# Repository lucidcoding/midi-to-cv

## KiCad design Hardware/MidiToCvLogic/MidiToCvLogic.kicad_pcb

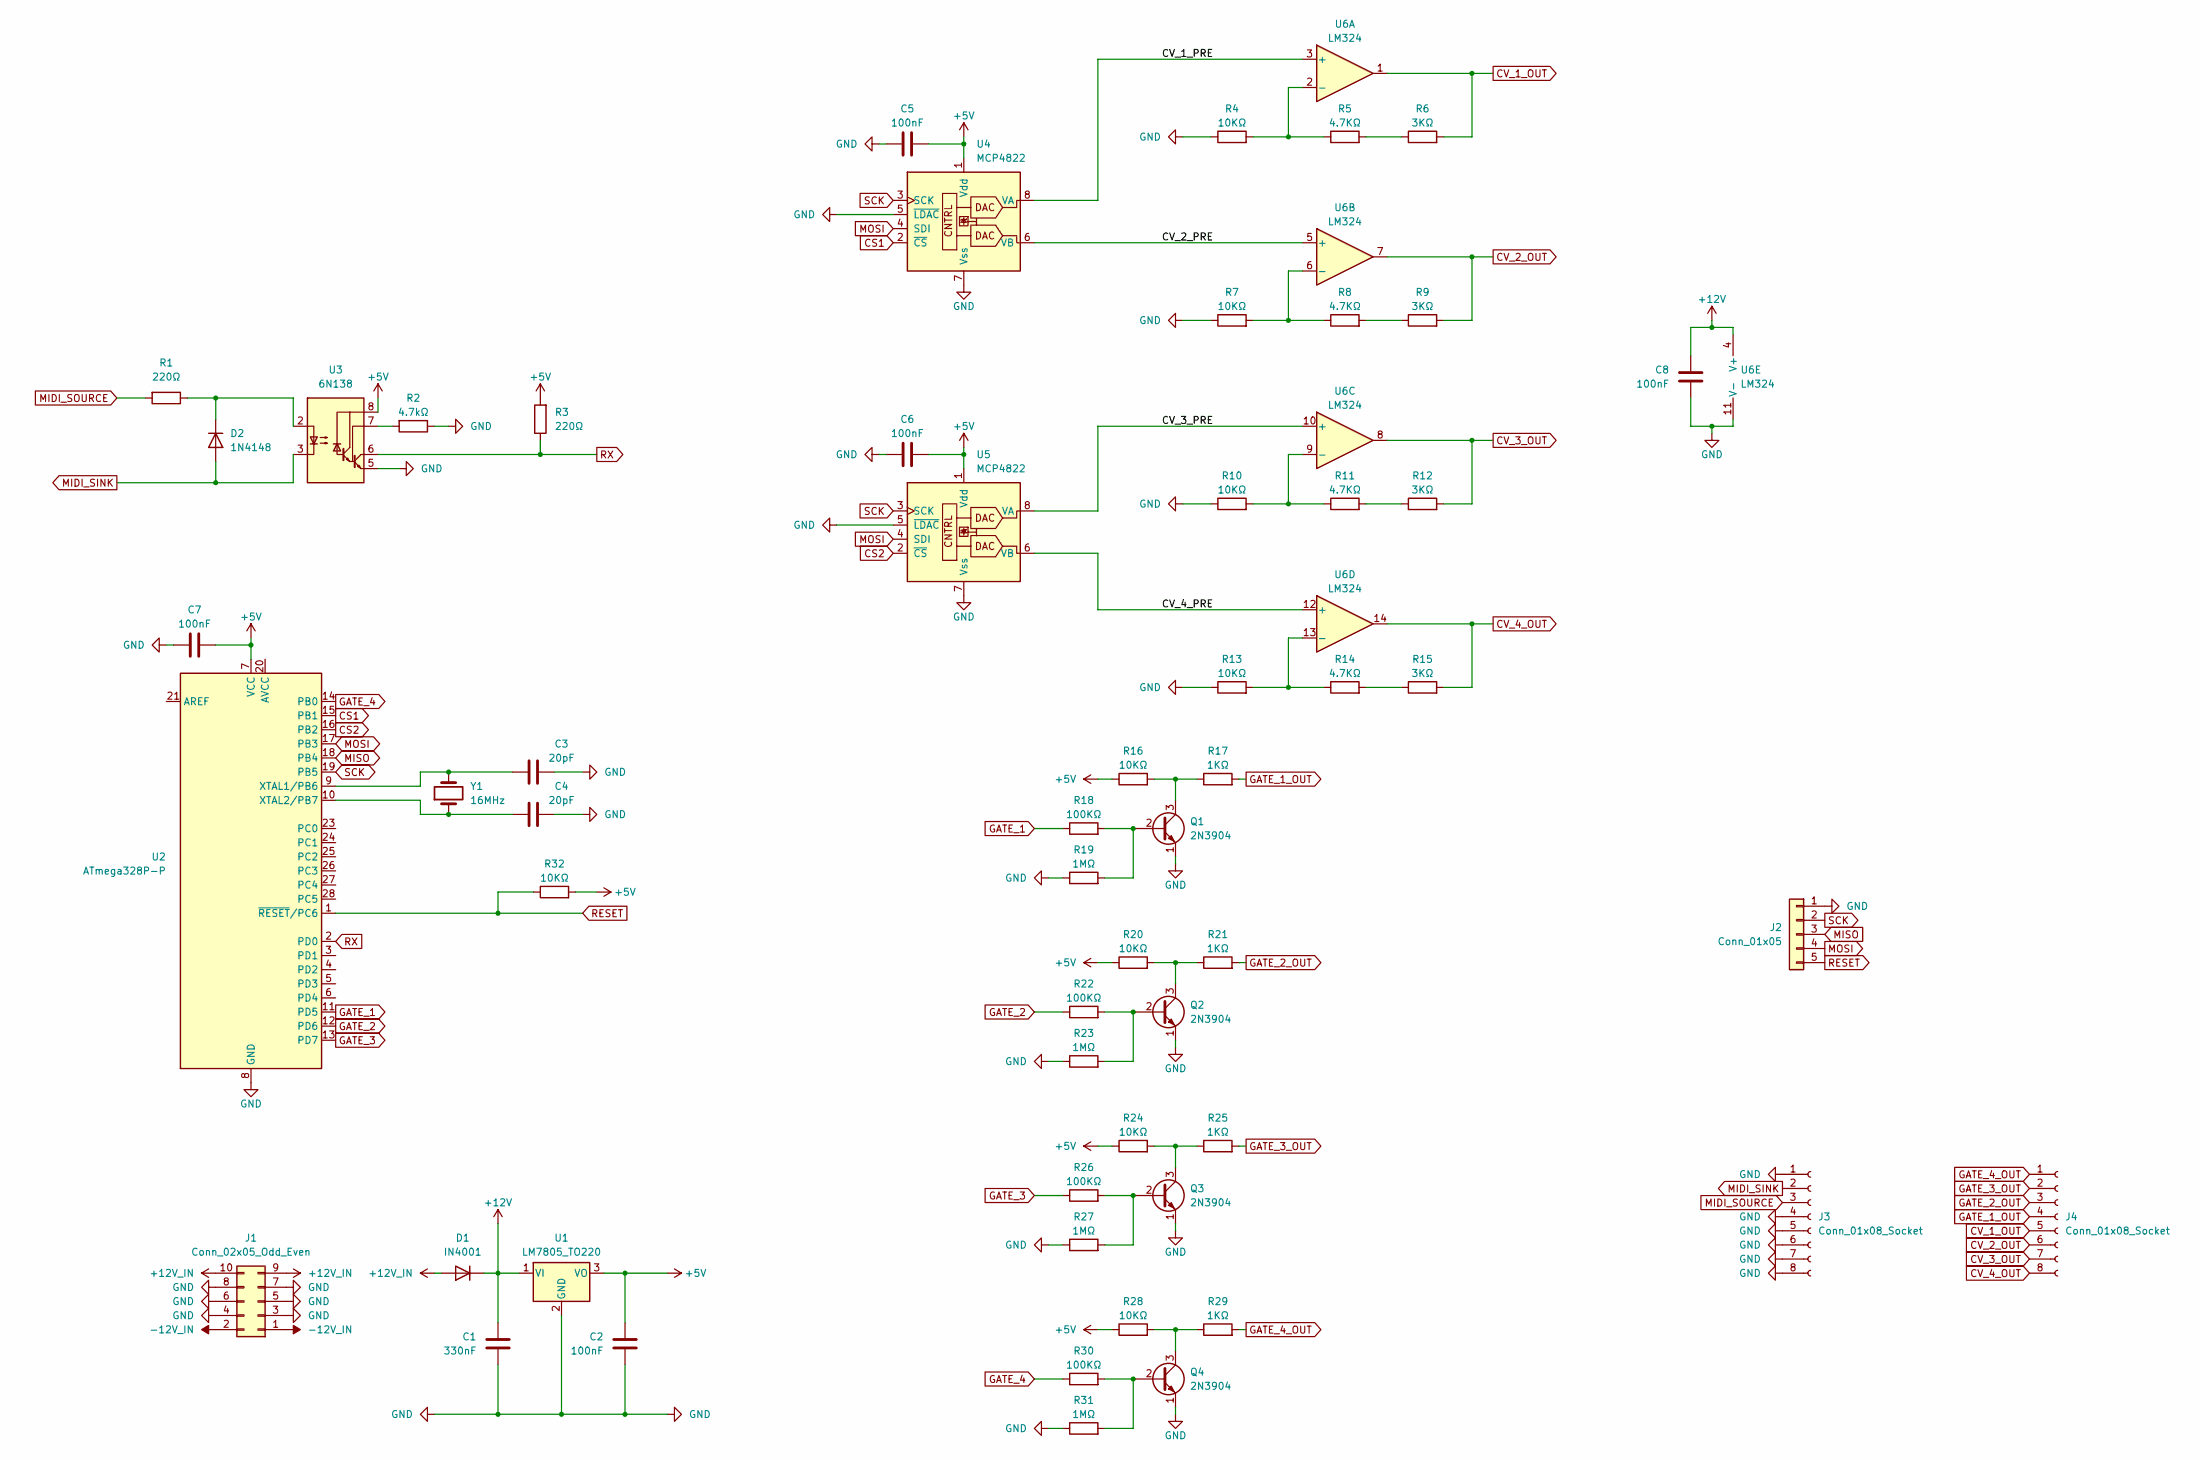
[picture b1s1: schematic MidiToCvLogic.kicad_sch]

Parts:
C1: 330nF; C_Disc_D5.0mm_W2.5mm_P5.00mm
C2, C8: 100nF; C_Disc_D5.0mm_W2.5mm_P5.00mm
C3, C4: 20pF; C_Disc_D3.0mm_W1.6mm_P2.50mm
C5, C6, C7: 100nF; C_Disc_D4.3mm_W1.9mm_P5.00mm
D1: IN4001; D_DO-35_SOD27_P7.62mm_Horizontal
D2: 1N4148; D_DO-35_SOD27_P7.62mm_Horizontal
J1: Conn_02x05_Odd_Even; IDC-Header_2x05_P2.54mm_Vertical
J2: Conn_01x05; JST_PH_B5B-PH-K_1x05_P2.00mm_Vertical
J3, J4: Conn_01x08_Socket; PinSocket_1x08_P2.54mm_Vertical
Q1, Q2, Q3, Q4: 2N3904; TO-92_Inline
R1, R3: 220Ω; R_Axial_DIN0207_L6.3mm_D2.5mm_P7.62mm_Horizontal
R2: 4.7kΩ; R_Axial_DIN0207_L6.3mm_D2.5mm_P7.62mm_Horizontal
R4, R7, R10, R13, R16, R20, R24, R32: 10KΩ; R_Axial_DIN0207_L6.3mm_D2.5mm_P7.62mm_Horizontal
R5, R8, R11, R14: 4.7KΩ; R_Axial_DIN0207_L6.3mm_D2.5mm_P7.62mm_Horizontal
R6, R9, R12, R15: 3KΩ; R_Axial_DIN0207_L6.3mm_D2.5mm_P7.62mm_Horizontal
R17, R21, R25: 1KΩ; R_Axial_DIN0207_L6.3mm_D2.5mm_P7.62mm_Horizontal
R18, R22, R26, R30: 100KΩ; R_Axial_DIN0207_L6.3mm_D2.5mm_P7.62mm_Horizontal
R19, R23, R27, R31: 1MΩ; R_Axial_DIN0207_L6.3mm_D2.5mm_P7.62mm_Horizontal
R28: 10KΩ; R_Axial_DIN0207_L6.3mm_D2.5mm_P7.62mm_Horizontal_Thin
R29: 1KΩ; R_Axial_DIN0207_L6.3mm_D2.5mm_P7.62mm_Horizontal_Thin
U1: LM7805_TO220; TO-220-3_Vertical
U2: ATmega328P-P; DIP-28_W7.62mm_Socket
U3: 6N138; DIP-8_W7.62mm_Socket
U4, U5: MCP4822; DIP-8_W7.62mm_Socket
U6: LM324; DIP-14_W7.62mm_Socket
Y1: 16MHz; Crystal_HC49-4H_Vertical

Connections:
+5V: C2.1, C5.2, C6.2, C7.2, R3.2, R16.1, R20.1, R24.1, R28.1, R32.2, U1.3 (VO), U2.7 (VCC), U3.8 (VCC), U4.1 (Vdd), U5.1 (Vdd)
+12V: C1.1, C8.1, D1.1 (K), U1.1 (VI), U6.4 (V+)
+12V_IN: D1.2 (A), J1.9, J1.10
-12V_IN: J1.1, J1.2
/CV_1_PRE: U4.8 (VA), U6.3 (+)
/CV_2_PRE: U4.6 (VB), U6.5 (+)
/CV_3_PRE: U5.8 (VA), U6.10 (+)
/CV_4_PRE: U5.6 (VB), U6.12 (+)
CS1: U2.15 (PB1), U4.2 (~CS)
CS2: U2.16 (PB2), U5.2 (~CS)
CV_1_OUT: J4.5, R6.2, U6.1
CV_2_OUT: J4.6, R9.2, U6.7
CV_3_OUT: J4.7, R12.2, U6.8
CV_4_OUT: J4.8, R15.2, U6.14
GATE_1: R18.1, U2.11 (PD5)
GATE_1_OUT: J4.4, R17.2
GATE_2: R22.1, U2.12 (PD6)
GATE_2_OUT: J4.3, R21.2
GATE_3: R26.1, U2.13 (PD7)
GATE_3_OUT: J4.2, R25.2
GATE_4: R30.1, U2.14 (PB0)
GATE_4_OUT: J4.1, R29.2
GND: C1.2, C2.2, C3.2, C4.2, C5.1, C6.1, C7.1, C8.2, J1.3, J1.4, J1.5, J1.6, J1.7, J1.8, J2.1, J3.1, J3.4, J3.5, J3.6, J3.7, J3.8, Q1.1 (E), Q2.1 (E), Q3.1 (E), Q4.1 (E), R2.1, R4.1, R7.1, R10.1, R13.1, R19.1, R23.1, R27.1, R31.1, U1.2 (GND), U2.8 (GND), U2.22 (GND), U3.5 (GND), U4.5 (~LDAC), U4.7 (Vss), U5.5 (~LDAC), U5.7 (Vss), U6.11 (V-)
MIDI_SINK: D2.2 (A), J3.2, U3.3 (C2)
MIDI_SOURCE: J3.3, R1.2
MISO: J2.3, U2.18 (PB4)
MOSI: J2.4, U2.17 (PB3), U4.4 (SDI), U5.4 (SDI)
unnamed: D2.1 (K), R1.1, U3.2 (C1)
unnamed: Q1.2 (B), R18.2, R19.2
unnamed: Q1.3 (C), R16.2, R17.1
unnamed: Q2.2 (B), R22.2, R23.2
unnamed: Q2.3 (C), R20.2, R21.1
unnamed: Q3.2 (B), R26.2, R27.2
unnamed: Q3.3 (C), R24.2, R25.1
unnamed: Q4.2 (B), R30.2, R31.2
unnamed: Q4.3 (C), R28.2, R29.1
unnamed: R5.2, R6.1
unnamed: R8.2, R9.1
unnamed: R11.2, R12.1
unnamed: R14.2, R15.1
unnamed: C3.1, U2.9 (XTAL1/PB6), Y1.2
unnamed: C4.1, U2.10 (XTAL2/PB7), Y1.1
unnamed: R2.2, U3.7 (VO1)
unnamed: R4.2, R5.1, U6.2 (-)
unnamed: R7.2, R8.1, U6.6 (-)
unnamed: R10.2, R11.1, U6.9 (-)
unnamed: R13.2, R14.1, U6.13 (-)
RESET: J2.5, R32.1, U2.1 (~RESET/PC6)
RX: R3.1, U2.2 (PD0), U3.6 (VO2)
SCK: J2.2, U2.19 (PB5), U4.3 (SCK), U5.3 (SCK)

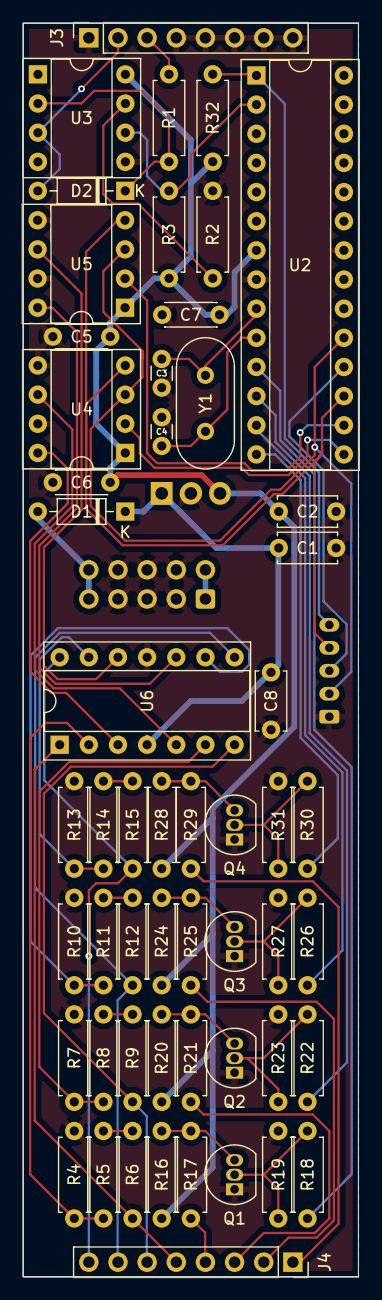
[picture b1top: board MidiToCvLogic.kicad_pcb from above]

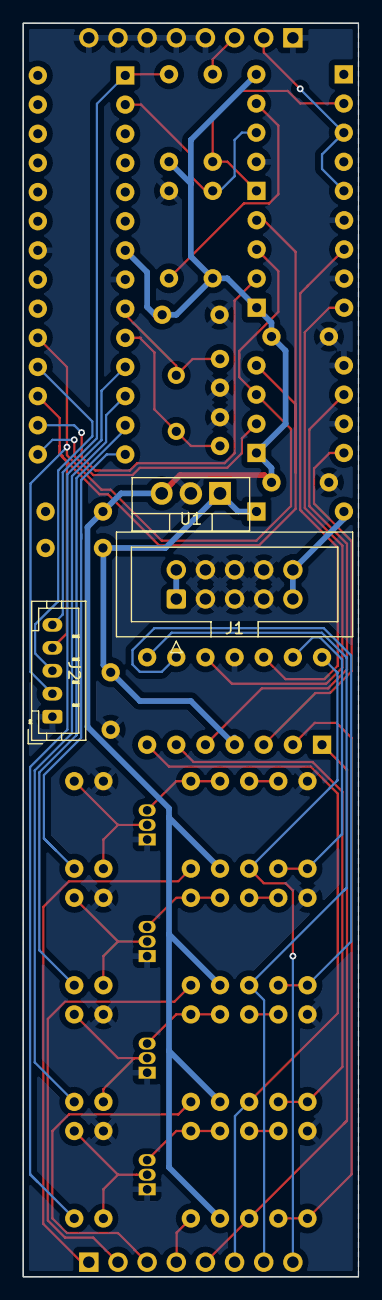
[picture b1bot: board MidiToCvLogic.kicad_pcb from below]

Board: 2 copper layers, 29.2 x 109.2 mm, 57 parts (3 on the bottom side), 50 nets.

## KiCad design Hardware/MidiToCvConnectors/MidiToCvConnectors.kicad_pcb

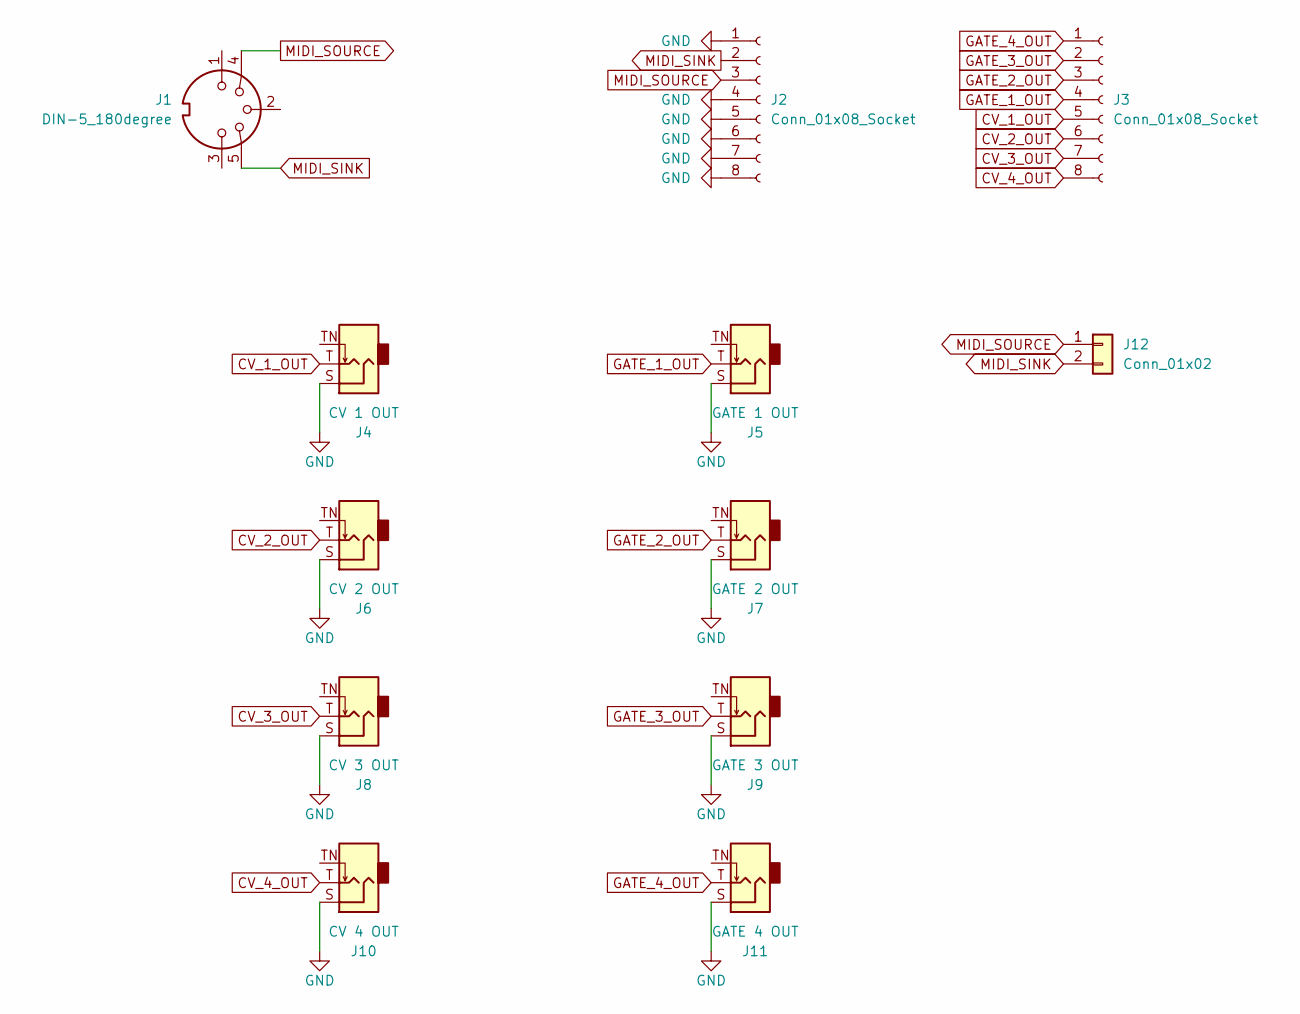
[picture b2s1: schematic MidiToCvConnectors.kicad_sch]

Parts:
J1: DIN-5_180degree; DIN_5_Vertical
J2, J3: Conn_01x08_Socket; PinHeader_1x08_P2.54mm_Vertical
J4: CV 1 OUT; Jack_3.5mm_QingPu_WQP-PJ301M-12_Vertical
J5: GATE 1 OUT; Jack_3.5mm_QingPu_WQP-PJ301M-12_Vertical
J6: CV 2 OUT; Jack_3.5mm_QingPu_WQP-PJ301M-12_Vertical
J7: GATE 2 OUT; Jack_3.5mm_QingPu_WQP-PJ301M-12_Vertical
J8: CV 3 OUT; Jack_3.5mm_QingPu_WQP-PJ301M-12_Vertical
J9: GATE 3 OUT; Jack_3.5mm_QingPu_WQP-PJ301M-12_Vertical
J10: CV 4 OUT; Jack_3.5mm_QingPu_WQP-PJ301M-12_Vertical
J11: GATE 4 OUT; Jack_3.5mm_QingPu_WQP-PJ301M-12_Vertical
J12: Conn_01x02; SolderWire-0.1sqmm_1x02_P3.6mm_D0.4mm_OD1mm

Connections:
CV_1_OUT: J3.5, J4.T
CV_2_OUT: J3.6, J6.T
CV_3_OUT: J3.7, J8.T
CV_4_OUT: J3.8, J10.T
GATE_1_OUT: J3.4, J5.T
GATE_2_OUT: J3.3, J7.T
GATE_3_OUT: J3.2, J9.T
GATE_4_OUT: J3.1, J11.T
GND: J2.1, J2.4, J2.5, J2.6, J2.7, J2.8, J4.S, J5.S, J6.S, J7.S, J8.S, J9.S, J10.S, J11.S
MIDI_SINK: J1.5, J2.2, J12.2
MIDI_SOURCE: J1.4, J2.3, J12.1

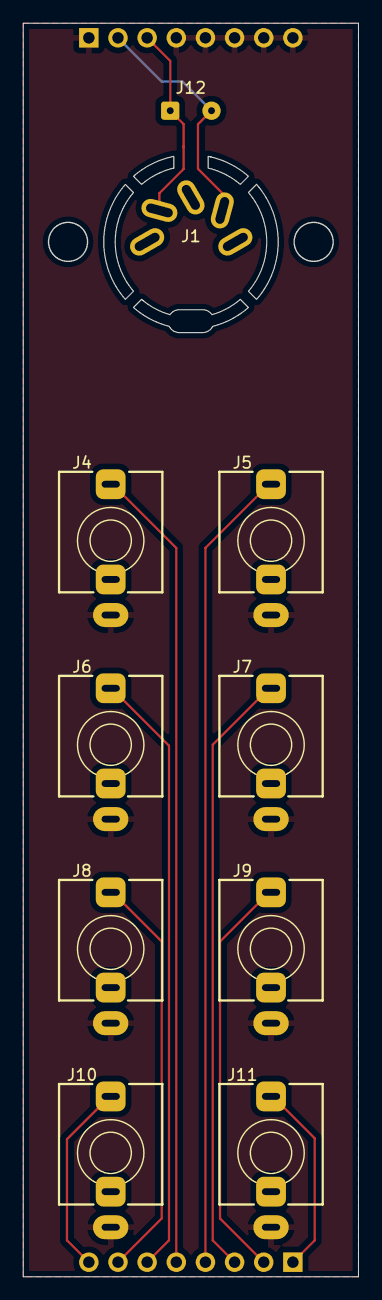
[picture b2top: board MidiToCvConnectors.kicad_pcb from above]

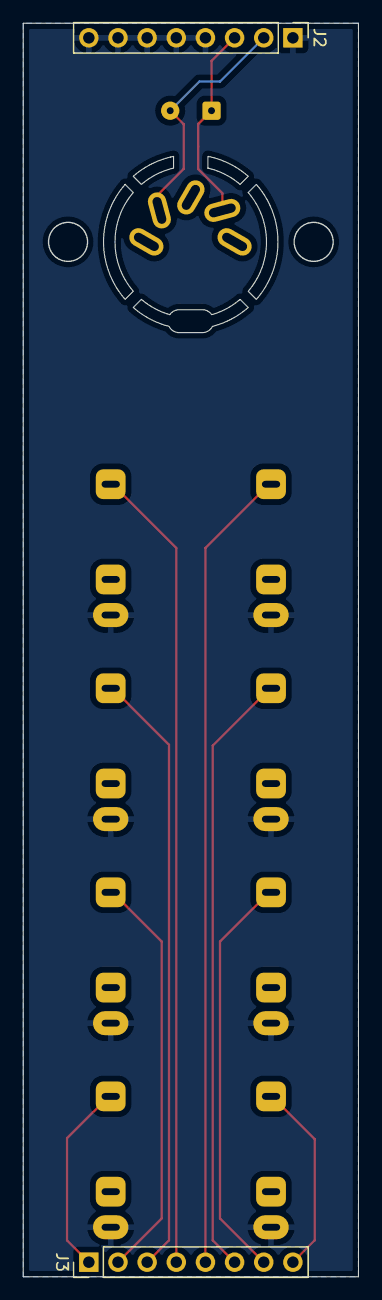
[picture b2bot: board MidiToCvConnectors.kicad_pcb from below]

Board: 2 copper layers, 29.1 x 109.1 mm, 12 parts (2 on the bottom side), 11 nets.

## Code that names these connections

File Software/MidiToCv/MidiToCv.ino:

#include <MIDI.h>
#include <SPI.h>

// MCP4822 DAC out
#define SPI_MOSI 11
#define SPI_MISO 12
#define SPI_SCK  13
#define SPI_CS_1 9
#define SPI_CS_2 10
#define GATE_1_PIN 5
#define GATE_2_PIN 6
#define GATE_3_PIN 7
#define GATE_4_PIN 8
#define NOTE_SF 47.069f 

MIDI_CREATE_DEFAULT_INSTANCE();

//SPISettings settingsA(16000000, MSBFIRST, SPI_MODE0);  // At 16 = SPI Clock = 8MHz.

void setup() {
  pinMode(SPI_CS_1, OUTPUT); 
  pinMode(SPI_CS_2, OUTPUT); 
  pinMode(GATE_1_PIN, OUTPUT); 
  pinMode(GATE_2_PIN, OUTPUT); 
  pinMode(GATE_3_PIN, OUTPUT); 
  pinMode(GATE_4_PIN, OUTPUT); 

  SPI.begin();
  //SPI.setClockDivider(SPI_CLOCK_DIV2); // 8 MHz
  //noInterrupts();

  MIDI.begin(MIDI_CHANNEL_OMNI);
}

void loop() {  

  if (MIDI.read()) { 

    int channel = MIDI.getChannel();

    byte gatePin, cv, cs, dacChannel, note;
    unsigned int voltage;
    
    switch(channel) {
      case 1:
        gatePin = GATE_1_PIN;
        cs = SPI_CS_1;
        dacChannel = 0;
        break;
      case 2:
        gatePin = GATE_2_PIN;
        cs = SPI_CS_1;
        dacChannel = 1;
        break;
      case 3:
        gatePin = GATE_3_PIN;
        cs = SPI_CS_2;
        dacChannel = 0;
        break;
      case 4:
        gatePin = GATE_4_PIN;
        cs = SPI_CS_2;
        dacChannel = 1;
        break;
    }
                   
    byte type = MIDI.getType();
     
    switch (type) {
      case midi::NoteOn: 
        note = MIDI.getData1();
        voltage = (unsigned int) ((float) note * NOTE_SF + 0.5); 
        setVoltage(cs, dacChannel, 1, voltage); 
        digitalWrite(gatePin, LOW);
        break;
      case midi::NoteOff:
        digitalWrite(gatePin, HIGH);
        break;
      default:
        break;
    }
  }
}

void setVoltage(byte cs, bool dacChannel, bool gain, unsigned int mV)
{
  unsigned int command = dacChannel ? 0x9000 : 0x1000;

  command |= gain ? 0x0000 : 0x2000;
  command |= (mV & 0x0FFF);
  
  SPI.beginTransaction(SPISettings(8000000, MSBFIRST, SPI_MODE0));
  digitalWrite(cs, LOW);
  SPI.transfer(command>>8);
  SPI.transfer(command&0xFF);
  digitalWrite(cs, HIGH);
  SPI.endTransaction();
}

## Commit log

2025-06-16 Schematic completed
2025-12-29 software added
